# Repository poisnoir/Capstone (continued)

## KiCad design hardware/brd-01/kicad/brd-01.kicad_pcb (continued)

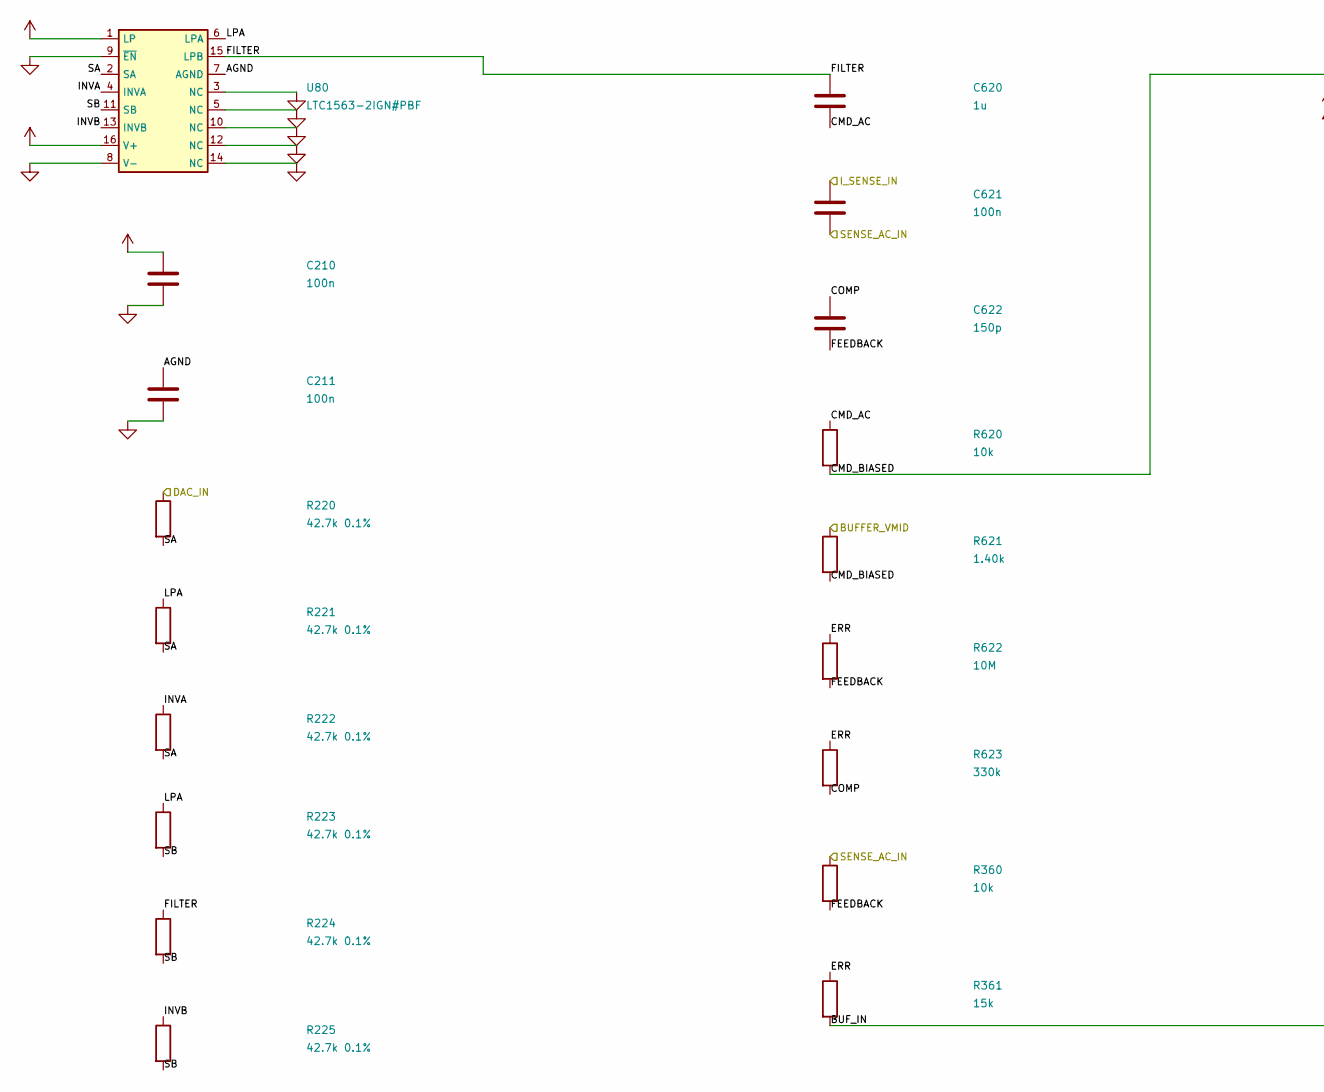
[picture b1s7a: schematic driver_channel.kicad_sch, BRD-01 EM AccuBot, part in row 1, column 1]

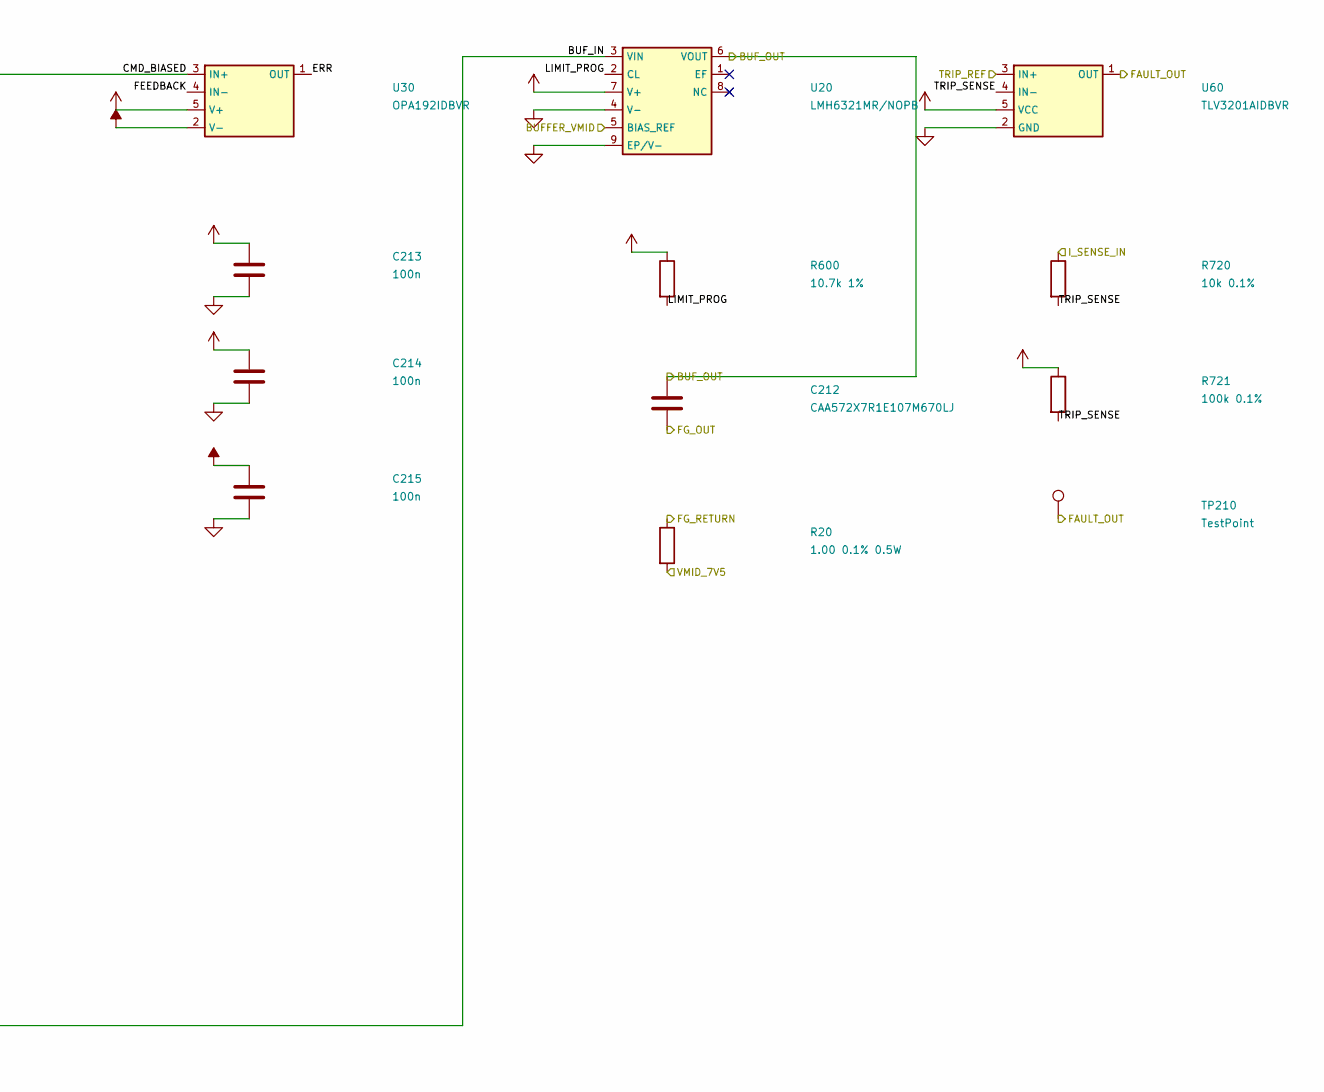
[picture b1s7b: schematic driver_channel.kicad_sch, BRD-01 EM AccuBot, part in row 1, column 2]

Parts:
C210, C211, C213, C214, C215, C621: 100n; C_0603_1608Metric
C212: CAA572X7R1E107M670LJ; TDK_CAA572
C620: 1u; C_0805_2012Metric
C622: 150p; C_0603_1608Metric
R20: 1.00 0.1% 0.5W; R_2512_6332Metric
R220, R221, R222, R223, R224, R225: 42.7k 0.1%; R_0603_1608Metric; MPN TNPW060342K7BEEA
R360, R620: 10k; R_0603_1608Metric
R361: 15k; R_0603_1608Metric
R600: 10.7k 1%; R_0603_1608Metric
R621: 1.40k; R_0603_1608Metric
R622: 10M; R_0603_1608Metric
R623: 330k; R_0603_1608Metric
R720: 10k 0.1%; R_0603_1608Metric
R721: 100k 0.1%; R_0603_1608Metric
TP210: TestPoint; TestPoint_Pad_D1.0mm
U20: LMH6321MR/NOPB; SOIC-8-1EP_3.9x4.9mm_P1.27mm_EP2.95x4.9mm_Mask2.71x3.4mm
U30: OPA192IDBVR; SOT-23-5
U60: TLV3201AIDBVR; SOT-23-5
U80: LTC1563-2IGN#PBF; SSOP-16_3.9x4.9mm_P0.635mm

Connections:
+3.3V: R721.1, U60.5 (VCC); also elsewhere on the board
+5V_EXC: C210.1, U80.1 (LP), U80.16 (V+); also elsewhere on the board
+12VA: C214.1, U30.5 (V+); also elsewhere on the board
+15V_FUSED: C213.1, R600.1, U20.7 (V+); also elsewhere on the board
-12VA: C215.1, U30.2 (V-); also elsewhere on the board
/driver/AGND0: C211.1, U80.7 (AGND)
/driver/BUF0: C212.1, U20.6 (VOUT); also elsewhere on the board
/driver/BUFFER_VMID: R621.1, U20.5 (BIAS_REF); also elsewhere on the board
/driver/BUF_IN0: R361.2, U20.3 (VIN)
/driver/CMD_AC0: C620.2, R620.1
/driver/CMD_BIASED0: R620.2, R621.2, U30.3 (IN+)
/driver/COMP0: C622.1, R623.2
/driver/DAC0: R220.1; also elsewhere on the board
/driver/ERR0: R361.1, R622.1, R623.1, U30.1 (OUT)
/driver/FAULT0: TP210.1 (1_1), U60.1 (OUT); also elsewhere on the board
/driver/FEEDBACK0: C622.2, R360.2, R622.2, U30.4 (IN-)
/driver/FILTER0: C620.1, R224.1, U80.15 (LPB)
/driver/INVA0: R222.1, U80.4 (INVA)
/driver/INVB0: R225.1, U80.13 (INVB)
/driver/I_SENSE0: C621.1, R720.1; also elsewhere on the board
/driver/LIMIT_PROG0: R600.2, U20.2 (CL)
/driver/LPA0: R221.1, R223.1, U80.6 (LPA)
/driver/SA0: R220.2, R221.2, R222.2, U80.2 (SA)
/driver/SB0: R223.2, R224.2, R225.2, U80.11 (SB)
/driver/SENSE_AC0: C621.2, R360.1
/driver/TRIP_REF: U60.3 (IN+); also elsewhere on the board
/driver/TRIP_SENSE0: R720.2, R721.2, U60.4 (IN-)
/driver/VMID_7V5: R20.2; also elsewhere on the board
FG0_OUT: C212.2; also elsewhere on the board
FG0_RETURN: R20.1; also elsewhere on the board
GND: C210.2, C211.2, C213.2, C214.2, C215.2, U20.4 (V-), U20.9 (EP/V-), U60.2 (GND), U80.3 (NC), U80.5 (NC), U80.8 (V-), U80.9 (~EN), U80.10 (NC), U80.12 (NC), U80.14 (NC); also elsewhere on the board

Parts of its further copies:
C218, C219, C221, C222, C223, C226, C227, C229, C230, C231, C234, C235, C237, C238, C239, C242, C243, C245, C246, C247, C250, C251, C253, C254, C255, C258, C259, C261, C262, C263, C266, C267, C269, C270, C271, C631, C641, C651, C661, C671, C681, C691: 100n; C_0603_1608Metric
C220, C228, C236, C244, C252, C260, C268: CAA572X7R1E107M670LJ; TDK_CAA572
C630, C640, C650, C660, C670, C680, C690: 1u; C_0805_2012Metric
C632, C642, C652, C662, C672, C682, C692: 150p; C_0603_1608Metric
R21, R22, R23, R24, R25, R26, R27: 1.00 0.1% 0.5W; R_2512_6332Metric
R230, R231, R232, R233, R234, R235, R240, R241, R242, R243, R244, R245, R250, R251, R252, R253, R254, R255, R260, R261, R262, R263, R264, R265, R270, R271, R272, R273, R274, R275, R280, R281, R282, R283, R284, R285, R290, R291, R292, R293, R294, R295: 42.7k 0.1%; R_0603_1608Metric; MPN TNPW060342K7BEEA
R362, R364, R366, R368, R370, R372, R374, R630, R640, R650, R660, R670, R680, R690: 10k; R_0603_1608Metric
R363, R365, R367, R369, R371, R373, R375: 15k; R_0603_1608Metric
R601, R602, R603, R604, R605, R606, R607: 10.7k 1%; R_0603_1608Metric
R631, R641, R651, R661, R671, R681, R691: 1.40k; R_0603_1608Metric
R632, R642, R652, R662, R672, R682, R692: 10M; R_0603_1608Metric
R633, R643, R653, R663, R673, R683, R693: 330k; R_0603_1608Metric
R722, R724, R726, R728, R730, R732, R734: 10k 0.1%; R_0603_1608Metric
R723, R725, R727, R729, R731, R733, R735: 100k 0.1%; R_0603_1608Metric
TP211, TP212, TP213, TP214, TP215, TP216, TP217: TestPoint; TestPoint_Pad_D1.0mm
U21, U22, U23, U24, U25, U26, U27: LMH6321MR/NOPB; SOIC-8-1EP_3.9x4.9mm_P1.27mm_EP2.95x4.9mm_Mask2.71x3.4mm
U31, U32, U33, U34, U35, U36, U37: OPA192IDBVR; SOT-23-5
U61, U62, U63, U64, U65, U66, U67: TLV3201AIDBVR; SOT-23-5
U81, U82, U83, U84, U85, U86, U87: LTC1563-2IGN#PBF; SSOP-16_3.9x4.9mm_P0.635mm

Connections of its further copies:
+3.3V: R723.1, R725.1, R727.1, R729.1, R731.1, R733.1, R735.1, U61.5 (VCC), U62.5 (VCC), U63.5 (VCC), U64.5 (VCC), U65.5 (VCC), U66.5 (VCC), U67.5 (VCC); also elsewhere on the board
+5V_EXC: C218.1, C226.1, C234.1, C242.1, C250.1, C258.1, C266.1, U81.1 (LP), U81.16 (V+), U82.1 (LP), U82.16 (V+), U83.1 (LP), U83.16 (V+), U84.1 (LP), U84.16 (V+), U85.1 (LP), U85.16 (V+), U86.1 (LP), U86.16 (V+), U87.1 (LP), U87.16 (V+); also elsewhere on the board
+12VA: C222.1, C230.1, C238.1, C246.1, C254.1, C262.1, C270.1, U31.5 (V+), U32.5 (V+), U33.5 (V+), U34.5 (V+), U35.5 (V+), U36.5 (V+), U37.5 (V+); also elsewhere on the board
+15V_FUSED: C221.1, C229.1, C237.1, C245.1, C253.1, C261.1, C269.1, R601.1, R602.1, R603.1, R604.1, R605.1, R606.1, R607.1, U21.7 (V+), U22.7 (V+), U23.7 (V+), U24.7 (V+), U25.7 (V+), U26.7 (V+), U27.7 (V+); also elsewhere on the board
-12VA: C223.1, C231.1, C239.1, C247.1, C255.1, C263.1, C271.1, U31.2 (V-), U32.2 (V-), U33.2 (V-), U34.2 (V-), U35.2 (V-), U36.2 (V-), U37.2 (V-); also elsewhere on the board
/driver/AGND1: C219.1, U81.7 (AGND)
/driver/AGND2: C227.1, U82.7 (AGND)
/driver/AGND3: C235.1, U83.7 (AGND)
/driver/AGND4: C243.1, U84.7 (AGND)
/driver/AGND5: C251.1, U85.7 (AGND)
/driver/AGND6: C259.1, U86.7 (AGND)
/driver/AGND7: C267.1, U87.7 (AGND)
/driver/BUF1: C220.1, U21.6 (VOUT)
/driver/BUF2: C228.1, U22.6 (VOUT)
/driver/BUF3: C236.1, U23.6 (VOUT)
/driver/BUF4: C244.1, U24.6 (VOUT)
/driver/BUF5: C252.1, U25.6 (VOUT)
/driver/BUF6: C260.1, U26.6 (VOUT)
/driver/BUF7: C268.1, U27.6 (VOUT)
/driver/BUFFER_VMID: R631.1, R641.1, R651.1, R661.1, R671.1, R681.1, R691.1, U21.5 (BIAS_REF), U22.5 (BIAS_REF), U23.5 (BIAS_REF), U24.5 (BIAS_REF), U25.5 (BIAS_REF), U26.5 (BIAS_REF), U27.5 (BIAS_REF); also elsewhere on the board
/driver/BUF_IN1: R363.2, U21.3 (VIN)
/driver/BUF_IN2: R365.2, U22.3 (VIN)
/driver/BUF_IN3: R367.2, U23.3 (VIN)
/driver/BUF_IN4: R369.2, U24.3 (VIN)
/driver/BUF_IN5: R371.2, U25.3 (VIN)
/driver/BUF_IN6: R373.2, U26.3 (VIN)
/driver/BUF_IN7: R375.2, U27.3 (VIN)
/driver/CMD_AC1: C630.2, R630.1
/driver/CMD_AC2: C640.2, R640.1
/driver/CMD_AC3: C650.2, R650.1
/driver/CMD_AC4: C660.2, R660.1
/driver/CMD_AC5: C670.2, R670.1
/driver/CMD_AC6: C680.2, R680.1
/driver/CMD_AC7: C690.2, R690.1
/driver/CMD_BIASED1: R630.2, R631.2, U31.3 (IN+)
/driver/CMD_BIASED2: R640.2, R641.2, U32.3 (IN+)
/driver/CMD_BIASED3: R650.2, R651.2, U33.3 (IN+)
/driver/CMD_BIASED4: R660.2, R661.2, U34.3 (IN+)
/driver/CMD_BIASED5: R670.2, R671.2, U35.3 (IN+)
/driver/CMD_BIASED6: R680.2, R681.2, U36.3 (IN+)
/driver/CMD_BIASED7: R690.2, R691.2, U37.3 (IN+)
/driver/COMP1: C632.1, R633.2
/driver/COMP2: C642.1, R643.2
/driver/COMP3: C652.1, R653.2
/driver/COMP4: C662.1, R663.2
/driver/COMP5: C672.1, R673.2
/driver/COMP6: C682.1, R683.2
/driver/COMP7: C692.1, R693.2
/driver/DAC1: R230.1; also elsewhere on the board
/driver/DAC2: R240.1; also elsewhere on the board
/driver/DAC3: R250.1; also elsewhere on the board
/driver/DAC4: R260.1; also elsewhere on the board
/driver/DAC5: R270.1; also elsewhere on the board
/driver/DAC6: R280.1; also elsewhere on the board
/driver/DAC7: R290.1; also elsewhere on the board
/driver/ERR1: R363.1, R632.1, R633.1, U31.1 (OUT)
/driver/ERR2: R365.1, R642.1, R643.1, U32.1 (OUT)
/driver/ERR3: R367.1, R652.1, R653.1, U33.1 (OUT)
/driver/ERR4: R369.1, R662.1, R663.1, U34.1 (OUT)
/driver/ERR5: R371.1, R672.1, R673.1, U35.1 (OUT)
/driver/ERR6: R373.1, R682.1, R683.1, U36.1 (OUT)
/driver/ERR7: R375.1, R692.1, R693.1, U37.1 (OUT)
/driver/FAULT1: TP211.1 (1_1), U61.1 (OUT); also elsewhere on the board
/driver/FAULT2: TP212.1 (1_1), U62.1 (OUT); also elsewhere on the board
/driver/FAULT3: TP213.1 (1_1), U63.1 (OUT); also elsewhere on the board
/driver/FAULT4: TP214.1 (1_1), U64.1 (OUT); also elsewhere on the board
/driver/FAULT5: TP215.1 (1_1), U65.1 (OUT); also elsewhere on the board
/driver/FAULT6: TP216.1 (1_1), U66.1 (OUT); also elsewhere on the board
/driver/FAULT7: TP217.1 (1_1), U67.1 (OUT); also elsewhere on the board
/driver/FEEDBACK1: C632.2, R362.2, R632.2, U31.4 (IN-)
/driver/FEEDBACK2: C642.2, R364.2, R642.2, U32.4 (IN-)
/driver/FEEDBACK3: C652.2, R366.2, R652.2, U33.4 (IN-)
/driver/FEEDBACK4: C662.2, R368.2, R662.2, U34.4 (IN-)
/driver/FEEDBACK5: C672.2, R370.2, R672.2, U35.4 (IN-)
/driver/FEEDBACK6: C682.2, R372.2, R682.2, U36.4 (IN-)
/driver/FEEDBACK7: C692.2, R374.2, R692.2, U37.4 (IN-)
/driver/FILTER1: C630.1, R234.1, U81.15 (LPB)
/driver/FILTER2: C640.1, R244.1, U82.15 (LPB)
/driver/FILTER3: C650.1, R254.1, U83.15 (LPB)
/driver/FILTER4: C660.1, R264.1, U84.15 (LPB)
/driver/FILTER5: C670.1, R274.1, U85.15 (LPB)
/driver/FILTER6: C680.1, R284.1, U86.15 (LPB)
/driver/FILTER7: C690.1, R294.1, U87.15 (LPB)
/driver/INVA1: R232.1, U81.4 (INVA)
/driver/INVA2: R242.1, U82.4 (INVA)
/driver/INVA3: R252.1, U83.4 (INVA)
/driver/INVA4: R262.1, U84.4 (INVA)
/driver/INVA5: R272.1, U85.4 (INVA)
/driver/INVA6: R282.1, U86.4 (INVA)
/driver/INVA7: R292.1, U87.4 (INVA)
/driver/INVB1: R235.1, U81.13 (INVB)
/driver/INVB2: R245.1, U82.13 (INVB)
/driver/INVB3: R255.1, U83.13 (INVB)
/driver/INVB4: R265.1, U84.13 (INVB)
/driver/INVB5: R275.1, U85.13 (INVB)
/driver/INVB6: R285.1, U86.13 (INVB)
/driver/INVB7: R295.1, U87.13 (INVB)
/driver/I_SENSE1: C631.1, R722.1; also elsewhere on the board
/driver/I_SENSE2: C641.1, R724.1; also elsewhere on the board
/driver/I_SENSE3: C651.1, R726.1; also elsewhere on the board
/driver/I_SENSE4: C661.1, R728.1; also elsewhere on the board
/driver/I_SENSE5: C671.1, R730.1; also elsewhere on the board
/driver/I_SENSE6: C681.1, R732.1; also elsewhere on the board
/driver/I_SENSE7: C691.1, R734.1; also elsewhere on the board
/driver/LIMIT_PROG1: R601.2, U21.2 (CL)
/driver/LIMIT_PROG2: R602.2, U22.2 (CL)
/driver/LIMIT_PROG3: R603.2, U23.2 (CL)
/driver/LIMIT_PROG4: R604.2, U24.2 (CL)
/driver/LIMIT_PROG5: R605.2, U25.2 (CL)
/driver/LIMIT_PROG6: R606.2, U26.2 (CL)
/driver/LIMIT_PROG7: R607.2, U27.2 (CL)
/driver/LPA1: R231.1, R233.1, U81.6 (LPA)
/driver/LPA2: R241.1, R243.1, U82.6 (LPA)
/driver/LPA3: R251.1, R253.1, U83.6 (LPA)
/driver/LPA4: R261.1, R263.1, U84.6 (LPA)
/driver/LPA5: R271.1, R273.1, U85.6 (LPA)
/driver/LPA6: R281.1, R283.1, U86.6 (LPA)
/driver/LPA7: R291.1, R293.1, U87.6 (LPA)
/driver/SA1: R230.2, R231.2, R232.2, U81.2 (SA)
/driver/SA2: R240.2, R241.2, R242.2, U82.2 (SA)
/driver/SA3: R250.2, R251.2, R252.2, U83.2 (SA)
/driver/SA4: R260.2, R261.2, R262.2, U84.2 (SA)
/driver/SA5: R270.2, R271.2, R272.2, U85.2 (SA)
/driver/SA6: R280.2, R281.2, R282.2, U86.2 (SA)
/driver/SA7: R290.2, R291.2, R292.2, U87.2 (SA)
/driver/SB1: R233.2, R234.2, R235.2, U81.11 (SB)
/driver/SB2: R243.2, R244.2, R245.2, U82.11 (SB)
/driver/SB3: R253.2, R254.2, R255.2, U83.11 (SB)
/driver/SB4: R263.2, R264.2, R265.2, U84.11 (SB)
/driver/SB5: R273.2, R274.2, R275.2, U85.11 (SB)
/driver/SB6: R283.2, R284.2, R285.2, U86.11 (SB)
/driver/SB7: R293.2, R294.2, R295.2, U87.11 (SB)
/driver/SENSE_AC1: C631.2, R362.1
/driver/SENSE_AC2: C641.2, R364.1
/driver/SENSE_AC3: C651.2, R366.1
/driver/SENSE_AC4: C661.2, R368.1
/driver/SENSE_AC5: C671.2, R370.1
/driver/SENSE_AC6: C681.2, R372.1
/driver/SENSE_AC7: C691.2, R374.1
/driver/TRIP_REF: U61.3 (IN+), U62.3 (IN+), U63.3 (IN+), U64.3 (IN+), U65.3 (IN+), U66.3 (IN+), U67.3 (IN+); also elsewhere on the board
/driver/TRIP_SENSE1: R722.2, R723.2, U61.4 (IN-)
/driver/TRIP_SENSE2: R724.2, R725.2, U62.4 (IN-)
/driver/TRIP_SENSE3: R726.2, R727.2, U63.4 (IN-)
/driver/TRIP_SENSE4: R728.2, R729.2, U64.4 (IN-)
/driver/TRIP_SENSE5: R730.2, R731.2, U65.4 (IN-)
/driver/TRIP_SENSE6: R732.2, R733.2, U66.4 (IN-)
/driver/TRIP_SENSE7: R734.2, R735.2, U67.4 (IN-)
/driver/VMID_7V5: R21.2, R22.2, R23.2, R24.2, R25.2, R26.2, R27.2; also elsewhere on the board
FG1_OUT: C220.2; also elsewhere on the board
FG1_RETURN: R21.1; also elsewhere on the board
FG2_OUT: C228.2; also elsewhere on the board
FG2_RETURN: R22.1; also elsewhere on the board
FG3_OUT: C236.2; also elsewhere on the board
FG3_RETURN: R23.1; also elsewhere on the board
FG4_OUT: C244.2; also elsewhere on the board
FG4_RETURN: R24.1; also elsewhere on the board
FG5_OUT: C252.2; also elsewhere on the board
FG5_RETURN: R25.1; also elsewhere on the board
FG6_OUT: C260.2; also elsewhere on the board
FG6_RETURN: R26.1; also elsewhere on the board
FG7_OUT: C268.2; also elsewhere on the board
FG7_RETURN: R27.1; also elsewhere on the board
GND: C218.2, C219.2, C221.2, C222.2, C223.2, C226.2, C227.2, C229.2, C230.2, C231.2, C234.2, C235.2, C237.2, C238.2, C239.2, C242.2, C243.2, C245.2, C246.2, C247.2, C250.2, C251.2, C253.2, C254.2, C255.2, C258.2, C259.2, C261.2, C262.2, C263.2, C266.2, C267.2, C269.2, C270.2, C271.2, U21.4 (V-), U21.9 (EP/V-), U22.4 (V-), U22.9 (EP/V-), U23.4 (V-), U23.9 (EP/V-), U24.4 (V-), U24.9 (EP/V-), U25.4 (V-), U25.9 (EP/V-), U26.4 (V-), U26.9 (EP/V-), U27.4 (V-), U27.9 (EP/V-), U61.2 (GND), U62.2 (GND), U63.2 (GND), U64.2 (GND), U65.2 (GND), U66.2 (GND), U67.2 (GND), U81.3 (NC), U81.5 (NC), U81.8 (V-), U81.9 (~EN), U81.10 (NC), U81.12 (NC), U81.14 (NC), U82.3 (NC), U82.5 (NC), U82.8 (V-), U82.9 (~EN), U82.10 (NC), U82.12 (NC), U82.14 (NC), U83.3 (NC), U83.5 (NC), U83.8 (V-), U83.9 (~EN), U83.10 (NC), U83.12 (NC), U83.14 (NC), U84.3 (NC), U84.5 (NC), U84.8 (V-), U84.9 (~EN), U84.10 (NC), U84.12 (NC), U84.14 (NC), U85.3 (NC), U85.5 (NC), U85.8 (V-), U85.9 (~EN), U85.10 (NC), U85.12 (NC), U85.14 (NC), U86.3 (NC), U86.5 (NC), U86.8 (V-), U86.9 (~EN), U86.10 (NC), U86.12 (NC), U86.14 (NC), U87.3 (NC), U87.5 (NC), U87.8 (V-), U87.9 (~EN), U87.10 (NC), U87.12 (NC), U87.14 (NC); also elsewhere on the board

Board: 2 copper layers, 636 parts (0 on the bottom side), 371 nets, no tracks yet.

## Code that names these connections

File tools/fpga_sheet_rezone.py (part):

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def zone_a(rz: Rezone):
    """DAC SPI series resistors and the CS pull-up beside U4 unit 2."""
    rz.detach(['R145', 'R146', 'R147', 'R162'],
              extra_labels=('DAC_CS_SRC', 'DAC_SCLK_SRC', 'DAC_SDI_SRC'))
    # the old FPGA-pin-to-label stubs are no longer used
    for ball in ('L4', 'M2', 'M1'):
        px, py = rz.pin('U4', ball)
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        rz.glabel(net, lab, 180 if ref in ('R145', 'R146') else 0)
        rz.prop_pos(ref, 'Reference', (15.24, row), 0)
        rz.prop_pos(ref, 'Value', (22.86, row), 0)
    # keep the pre-existing DAC_SDO flag on its own pin, off the new jog wire
    rz.label_at('global_label', 'DAC_SDO', (21.59, 57.15), (21.59, 57.15), 180)
    rz.label_at('global_label', 'PICO_RX', (21.59, 64.77), (21.59, 64.77), 0)
    rz.label_at('global_label', 'PICO_TX', (21.59, 67.31), (21.59, 67.31), 0)
    rz.move('R162', (15.24, 31.75), rot=0)
    p1, p2 = rz.pin('R162', '1'), rz.pin('R162', '2')
    rz.glabel('+3.3V', (p1[0], p1[1] - 3.81), 90)
    rz.wire(p1, (p1[0], p1[1] - 3.81), 'r162rail')
    rz.wire(p2, (20.32, p2[1]), 'r162cs')
    rz.glabel('DAC_CS', (20.32, p2[1]), 0)


def zone_b(rz: Rezone):
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        rz.prop_pos(ref, 'Reference', (cx, row - 3.81))
        rz.prop_pos(ref, 'Value', (cx, row + 3.81))
    px, py = rz.pin('U4', 'D13')
    rz.del_label_at('global_label', 'CLOCK_32M768', (295.91, py))
    rz.move('Y1', (321.31, py - 2.54), rot=180)
    out = rz.pin('Y1', '3')
    rz.wire(out, (px, py), 'clk')
    rz.glabel('CLOCK_32M768', (px, py), 0)
    for pin_no, net in (('1', '+3.3V'), ('4', '+3.3V'), ('2', 'GND')):
        p = rz.pin('Y1', pin_no)
        end = (p[0] + 5.08, p[1])
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    rz.prop_pos('U141', 'Value', (445.77, fy + 6.35))
    rz.wire(rz.pin('R790', '2'), rz.pin('U141', '6'), 'flashclk')
    # QSPI nets are local labels on this sheet in the baseline netlist.
    for net, fpin, side in (('QSPI_CS', '1', -1), ('QSPI_D0', '5', 1),
                            ('QSPI_D1', '2', 1), ('QSPI_D2', '3', 1),
                            ('QSPI_D3', '7', 1)):
        p = rz.pin('U141', fpin)
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    rz.del_wire((431.80, 298.45), (431.80, 307.34))   # old VBUS divider stub
    rz.del_wire((330.20, 292.10), (335.28, 292.10))   # old CBUS2 label stub
    cb2 = rz.pin('U142', '7')
    rz.del_label_at('label', 'VBUS_SENSE', cb2)       # superseded pin-side flag
    rz.del_label_at('label', 'VBUS_SENSE', (335.28, cb2[1]))
    tap = (342.90, cb2[1])
    rz.move('R158', (342.90, cb2[1] - 3.81), rot=0)
    rz.move('R159', (342.90, cb2[1] + 3.81), rot=0)
    rz.glabel('USB_VBUS', rz.pin('R158', '1'), 0)
    rz.wire(rz.pin('R158', '2'), tap, 'vbus-top')
    rz.wire(cb2, tap, 'vbus-tap')
    rz.wire(rz.pin('R159', '1'), tap, 'vbus-bot')
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    # Sense flag on a stub end, clear of both the junction dot and CBUS2 text.
    sense_end = (tap[0] + 7.62, tap[1])
    rz.wire(tap, sense_end, 'vbus-sense-stub')
    rz.llabel('VBUS_SENSE', sense_end, 0)
    for i, ref in enumerate(('C143', 'C144', 'C145')):
        rz.move(ref, (254.00, 250.19 + i * 10.16), rot=0)
        rz.glabel('+3.3V', rz.pin(ref, '1'), 0)
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            rz.prop_pos(ref, 'Value', (x + 3.81, y), 0)
    # Keep labels off wire interiors: move the two bridge labels and the XADC
    # tap to wire corners, and alternate the dense top rail flags.
    rz.label_at('label', 'FT_DP', (289.56, 274.32), (276.86, 274.32))
    rz.label_at('label', 'FT_DM', (289.56, 271.78), (276.86, 271.78))
    # XADC_VP stays at its baseline anchor: (427.99,140.97) belongs to
    # PROGRAM_B_0, so relocating the flag there would merge two nets.
    # Restore baseline angles on the dense +3.3V flag bank at y=33.02.
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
